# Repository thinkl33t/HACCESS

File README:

Hackspace Access Control/Card Entry Sentry System
=================================================

Access Control nodes for the hackspace

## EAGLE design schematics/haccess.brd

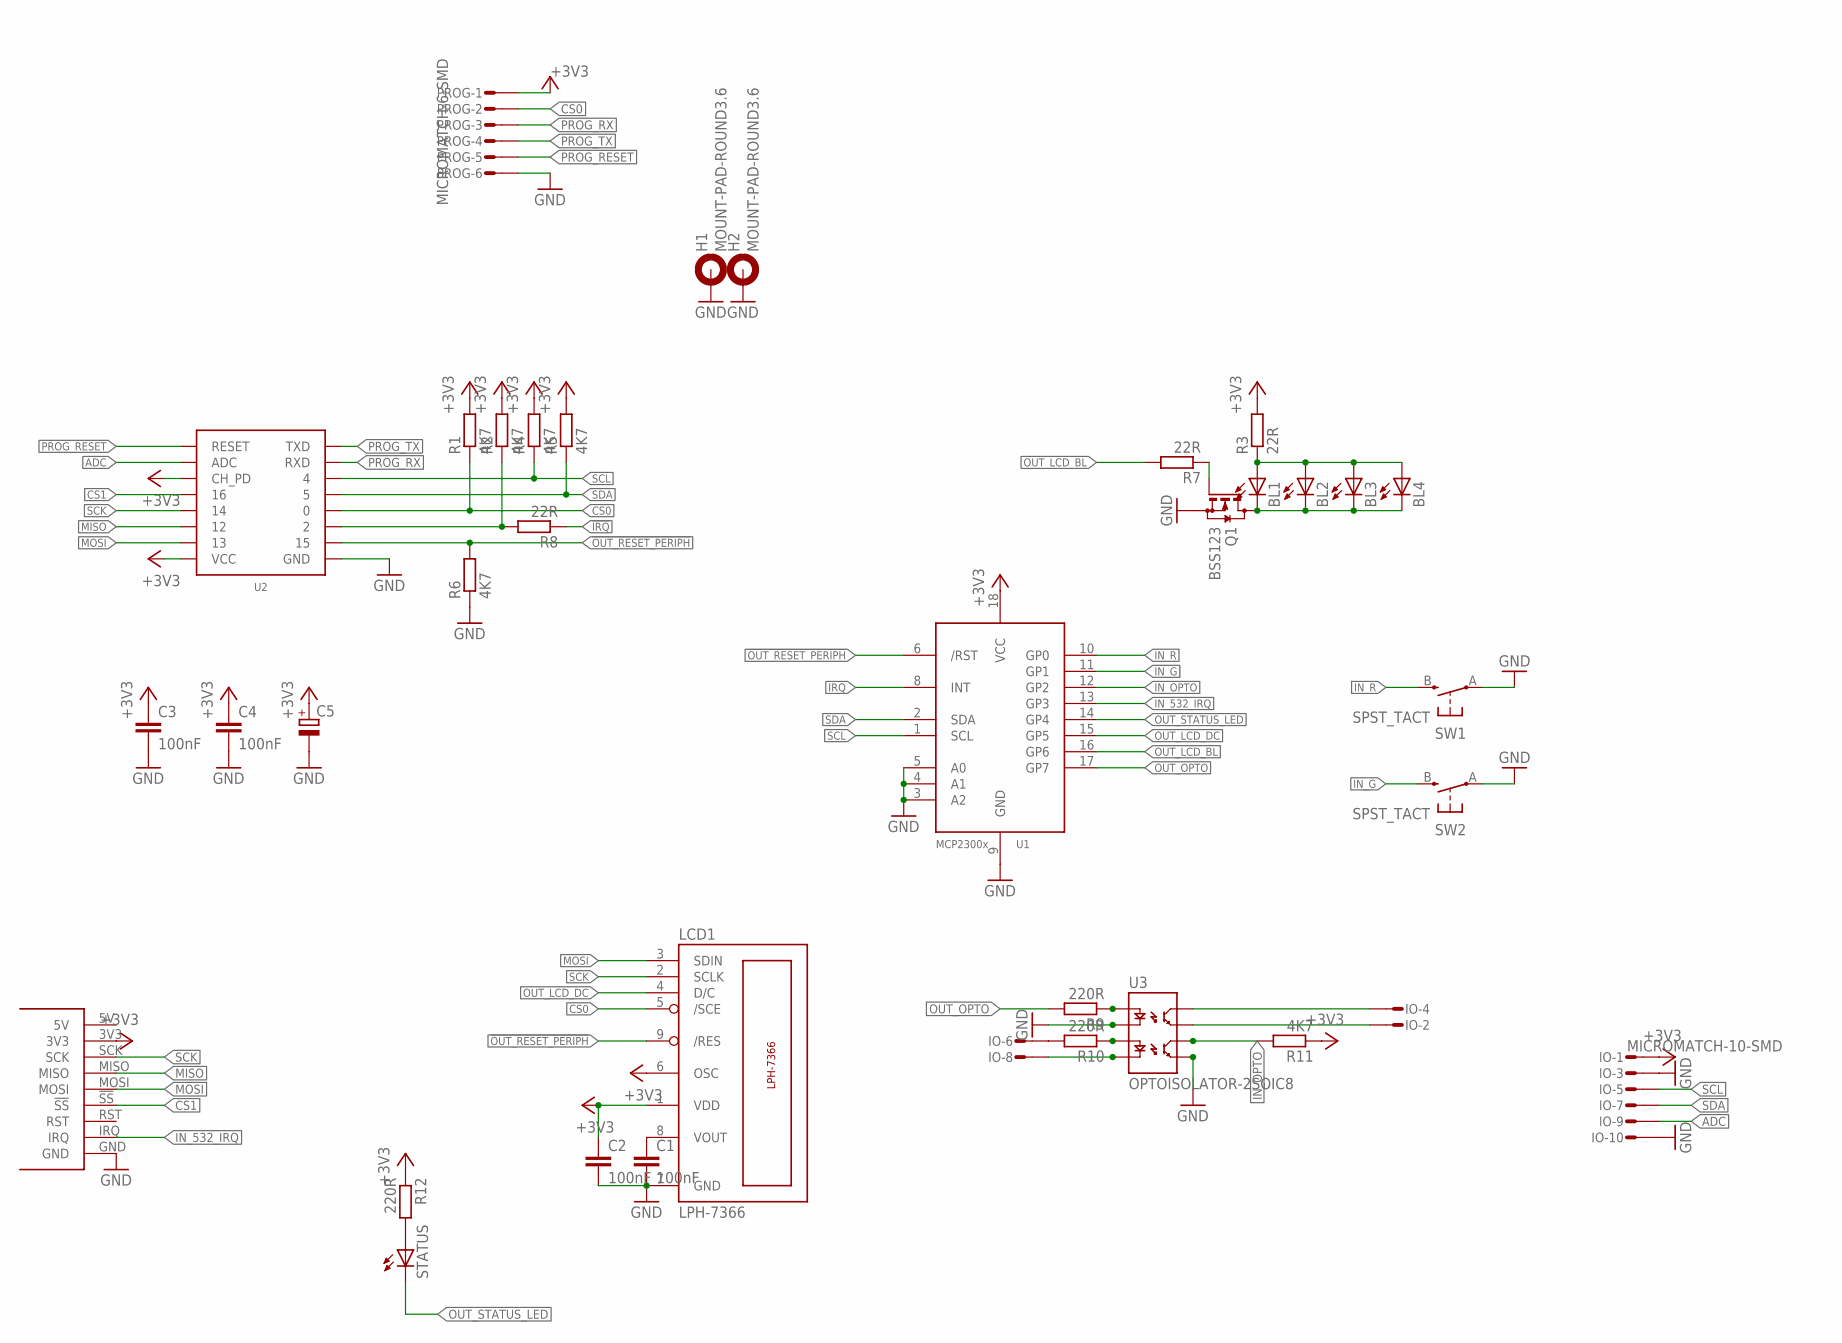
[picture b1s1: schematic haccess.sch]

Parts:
BL1, BL2, BL3, BL4: LEDCHIPLED_0805; CHIPLED_0805
C1, C2, C3, C4: 100nF; C0805K
C5: CPOL-EUSMCB; SMC_B
H1, H2: MOUNT-PAD-ROUND3.6; 3,6-PAD
IO: MICROMATCH-10-SMD
LCD1: LPH-7366
PROG: MICROMATCH-6-SMD
Q1: BSS123; SOT23
R1, R2, R4, R5, R6, R11: 4K7; R0603
R3, R7, R8: 22R; R0603
R9, R10, R12: 220R; R0603
STATUS: LEDCHIP-LED0805; CHIP-LED0805
SW1, SW2: SPST_TACT; SKPMAPE010
U1: MCP2300X/SO; SO18W
U2: ESP826607B; ESP-07B
U3: OPTOISOLATOR-2SOIC8; SO08-2
U$1: PN532SMALLMODULE; SMALL-MODULE

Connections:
!IRQ: R8.1, U1.8 (INT)
!IRQ_1: R2.1, R8.2, U2.GPIO2 (2)
!OUT_RESET_PERIPH: LCD1.9 (/RES), R6.2, U1.6 (/RST), U2.GPIO15 (15)
+3V3: C2.1, C3.1, C4.1, C5.+, IO.1, LCD1.1 (VDD), LCD1.6 (OSC), PROG.1, R1.2, R2.2, R3.2, R4.2, R5.2, R11.1, R12.1, U1.18 (VCC), U2.CH_PD, U2.VCC, U$1.3V3
ADC: IO.9, U2.ADC
CS0: LCD1.5 (/SCE), PROG.2, R1.1, U2.GPIO0 (0)
CS1: U2.GPIO16 (16), U$1.!SS
GND: C1.2, C2.2, C3.2, C4.2, C5.-, H1.B3,6, H2.B3,6, IO.3, IO.10, LCD1.7 (GND), PROG.6, Q1.2 (S), R6.1, SW1.A, SW2.A, U1.3 (A2), U1.4 (A1), U1.5 (A0), U1.9 (GND), U2.GND, U3.2 (C1), U3.5 (EM2), U$1.GND
IN_532_IRQ: U1.13 (GP3), U$1.IRQ
IN_G: SW2.B (S), U1.11 (GP1)
IN_OPTO: R11.2, U1.12 (GP2), U3.6 (CL2)
IN_OPTO_A: IO.6, R10.2
IN_OPTO_C: IO.8, U3.4 (C2)
IN_R: SW1.B (S), U1.10 (GP0)
MISO: U2.GPIO12 (12), U$1.MISO
MOSI: LCD1.3 (SDIN), U2.GPIO13 (13), U$1.MOSI
unnamed: C1.1, LCD1.8 (VOUT)
unnamed: R12.2, STATUS.A
unnamed: R9.1, U3.1 (A1)
unnamed: R10.1, U3.3 (A2)
unnamed: IO.4, U3.8 (CL1)
unnamed: IO.2, U3.7 (EM1)
unnamed: BL1.C, BL2.C, BL3.C, BL4.C, Q1.3 (D)
unnamed: BL1.A, BL2.A, BL3.A, BL4.A, R3.1
unnamed: Q1.1 (G), R7.1
OUT_LCD_BL: R7.2, U1.16 (GP6)
OUT_LCD_DC: LCD1.4 (D/C), U1.15 (GP5)
OUT_OPTO: R9.2, U1.17 (GP7)
OUT_STATUS_LED: STATUS.C, U1.14 (GP4)
PROG_RESET: PROG.5, U2.RESET
PROG_RX: PROG.3, U2.RXD
PROG_TX: PROG.4, U2.TXD
SCK: LCD1.2 (SCLK), U2.GPIO14 (14), U$1.SCK
SCL: IO.5, R4.1, U1.1 (SCL), U2.GPIO4 (4)
SDA: IO.7, R5.1, U1.2 (SDA), U2.GPIO5 (5)

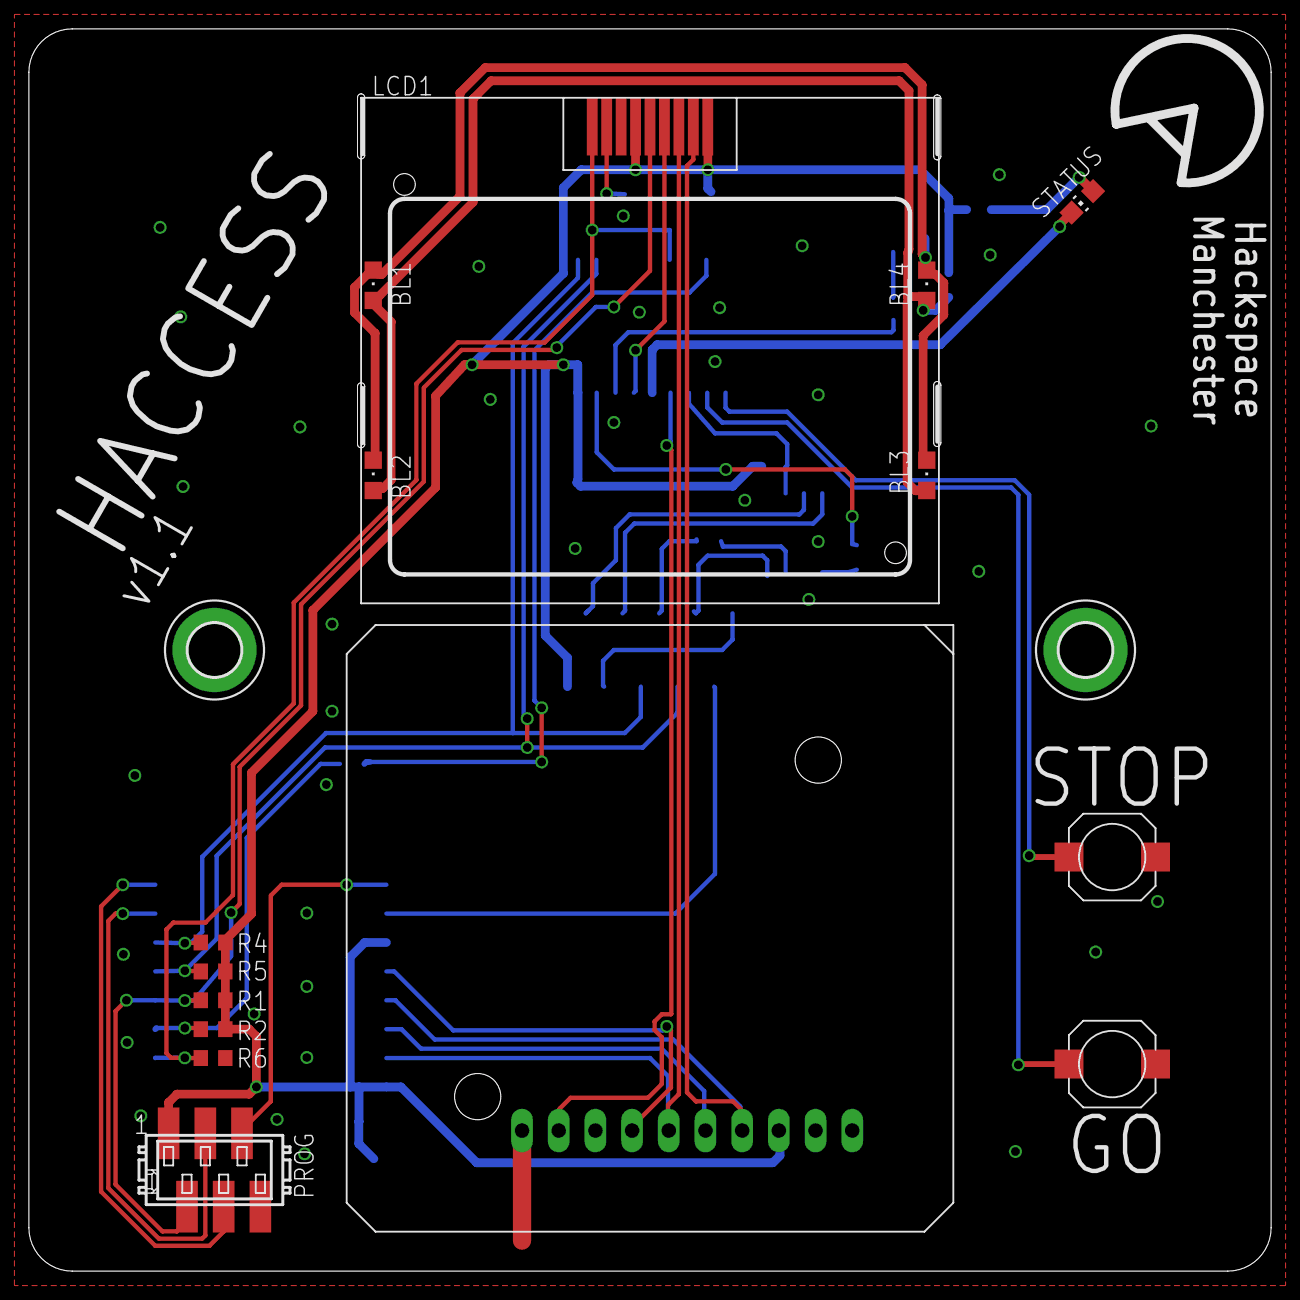
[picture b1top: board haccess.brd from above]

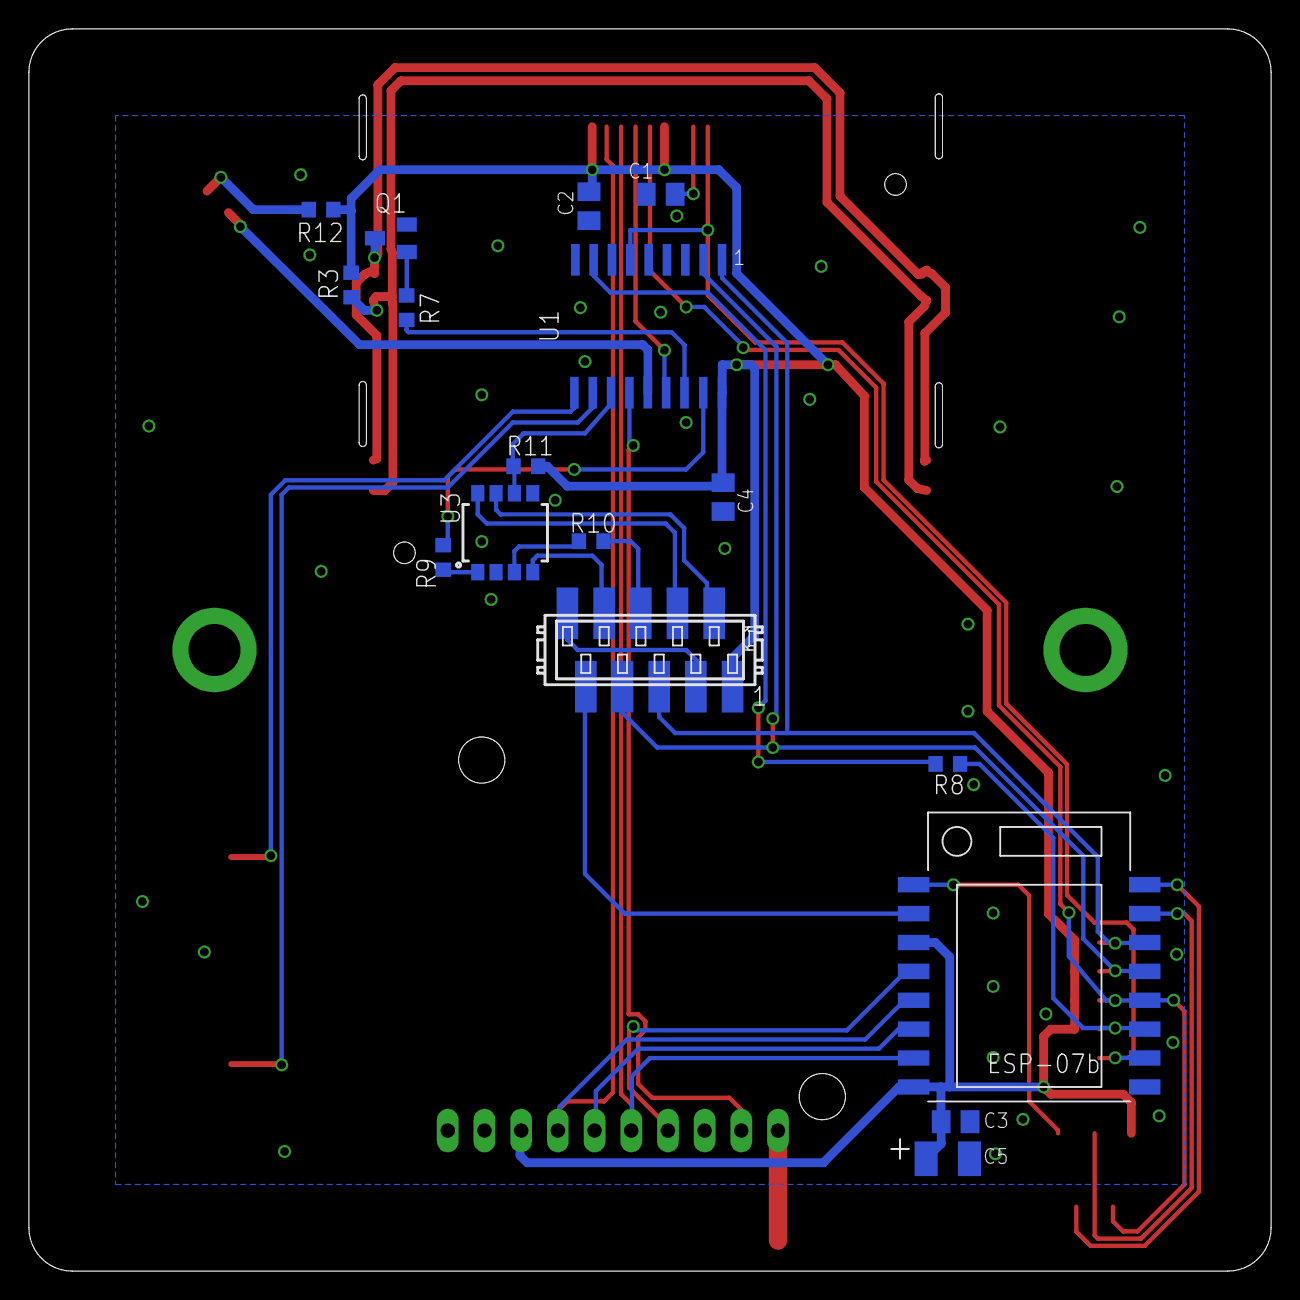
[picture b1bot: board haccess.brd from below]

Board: 2 copper layers, 86.0 x 86.0 mm, 34 parts (17 on the bottom side), 35 nets.

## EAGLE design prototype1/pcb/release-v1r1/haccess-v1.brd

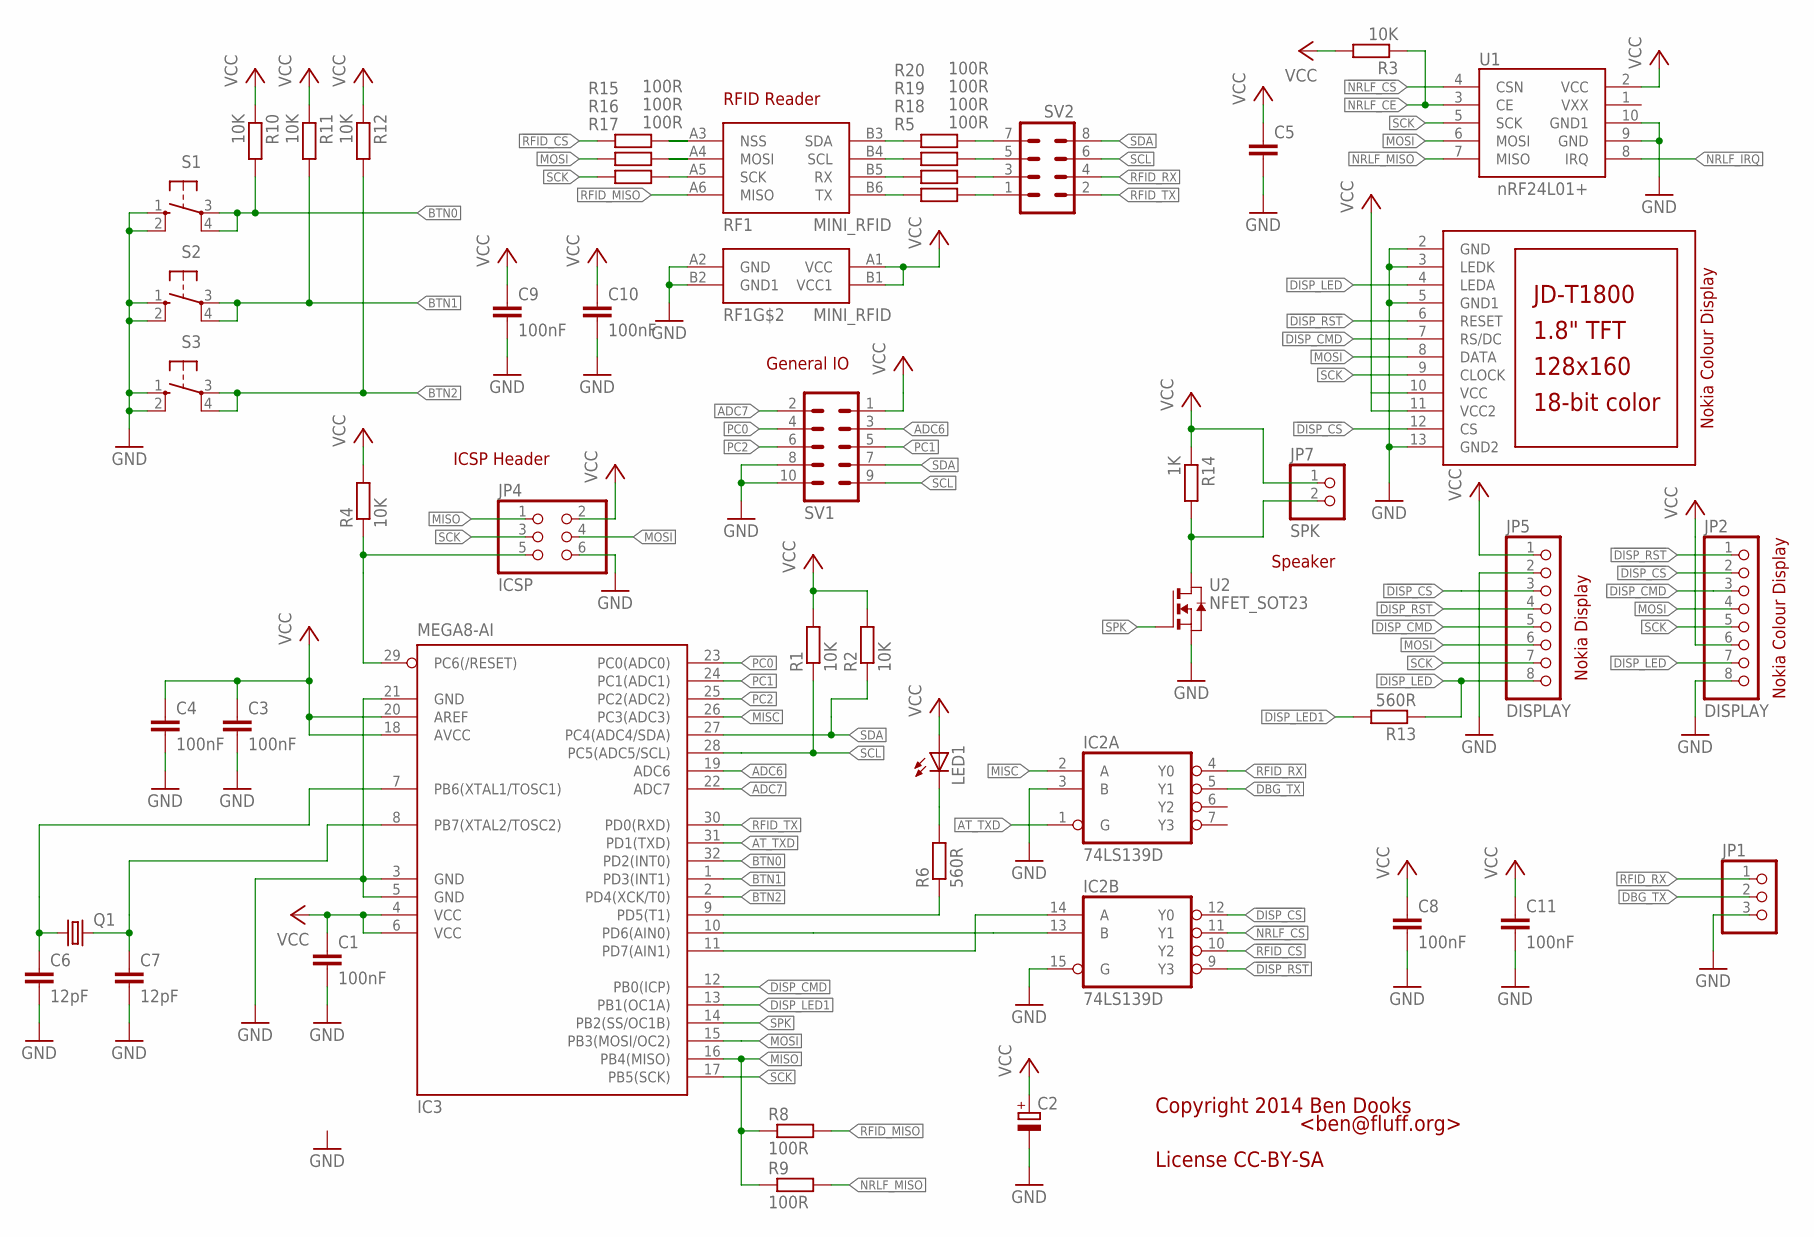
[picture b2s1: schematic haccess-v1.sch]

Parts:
C1, C9, C10: 100nF; C025-030X050
C2: CPOL-EUE2.5-6; E2,5-6
C3, C4, C8, C11: 100nF; C0603K
C5: C-EU025-030X050; C025-030X050
C6, C7: 12pF; C0603K
IC2: 74LS139D; SO16
IC3: MEGA8-AI; TQFP32-08
JP1: PINHD-1X3; 1X03
JP2, JP5: DISPLAY; 1X08
JP4: ICSP; 2X03
JP7: SPK; 1X02
LCD1: JD-T1800
LED1: LED5MM
Q1: CRYSTALHC49S; HC49/S
R1, R2, R3, R4, R10, R11, R12: 10K; R0603
R5, R18, R19, R20: 100R; R0603
R6: 560R; R0603
R8, R9: 100R; 0204/7
R13: 560R; 0204/7
R14: 1K; R0603
R15, R16: 100R; 0207/10
R17: 100R; 0207/7
RF1: MINI_RFID
S1, S2, S3: 10-XX; B3F-10XX
SV1: MA05-2
SV2: MA04-2
U1: NRF24L01+CHINESE-10PIN; CHINESE-10PIN
U2: NFET_SOT23; SOT23

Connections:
!DISP_CS: IC2.12 (Y0), JP2.2, JP5.3, LCD1.12 (CS)
!DISP_RST: IC2.9 (Y3), JP2.1, JP5.4, LCD1.6 (RESET)
!NRLF_CS: IC2.11 (Y1), U1.4 (CSN)
!RESET: IC3.29 (PC6(/RESET)), JP4.5, R4.1
!RFID_CS: IC2.10 (Y2), R15.1
ADC6: IC3.19 (ADC6), SV1.3
ADC7: IC3.22 (ADC7), SV1.2
AT_TXD: IC2.1 (G), IC3.31 (PD1(TXD))
BTN0: IC3.32 (PD2(INT0)), R10.2, S1.3, S1.4 (P1)
BTN1: IC3.1 (PD3(INT1)), R11.2, S2.3, S2.4 (P1)
BTN2: IC3.2 (PD4(XCK/T0)), R12.2, S3.3, S3.4 (P1)
DBG_TX: IC2.5 (Y1), JP1.2
DISP_CMD: IC3.12 (PB0(ICP)), JP2.3, JP5.5, LCD1.7 (RS/DC)
DISP_LED: JP2.7, JP5.8, LCD1.4 (LEDA), R13.1
DISP_LED1: IC3.13 (PB1(OC1A)), R13.2
GND: C1.2, C2.-, C3.2, C4.2, C5.2, C6.2, C7.2, C8.2, C9.2, C10.2, C11.2, IC2.3 (B), IC2.8 (GND), IC2.15 (G), IC3.3 (GND), IC3.5 (GND), IC3.21 (GND), JP1.3, JP2.8, JP4.6, JP5.2, LCD1.2 (GND), LCD1.3 (LEDK), LCD1.5 (GND1), LCD1.13 (GND2), RF1.A2 (GND), RF1.B2 (GND1), S1.1 (S), S1.2 (S1), S2.1 (S), S2.2 (S1), S3.1 (S), S3.2 (S1), SV1.8, SV1.10, U1.9 (GND), U1.10 (GND1), U2.2 (S)
LED: IC3.9 (PD5(T1)), R6.1
LED1: LED1.K (C), R6.2
MISC: IC2.2 (A), IC3.26 (PC3(ADC3))
MISO: IC3.16 (PB4(MISO)), JP4.1, R8.1, R9.1
MOSI: IC3.15 (PB3(MOSI/OC2)), JP2.4, JP4.4, JP5.6, LCD1.8 (DATA), R16.1, U1.6 (MOSI)
unnamed: R17.2, RF1.A5 (SCK)
unnamed: R16.2, RF1.A4 (MOSI)
unnamed: R15.2, RF1.A3 (NSS)
unnamed: R5.1, RF1.B6 (TX)
unnamed: R18.1, RF1.B5 (RX)
unnamed: R19.1, RF1.B4 (SCL)
unnamed: R20.1, RF1.B3 (SDA)
unnamed: R20.2, SV2.7
unnamed: IC2.13 (B), IC3.10 (PD6(AIN0))
unnamed: R19.2, SV2.5
unnamed: IC2.14 (A), IC3.11 (PD7(AIN1))
unnamed: R18.2, SV2.3
unnamed: R5.2, SV2.1
NRLF_CE: R3.1, U1.3 (CE)
NRLF_IRQ: U1.8 (IRQ)
NRLF_MISO: R9.2, U1.7 (MISO)
PC0: IC3.23 (PC0(ADC0)), SV1.4
PC1: IC3.24 (PC1(ADC1)), SV1.5
PC2: IC3.25 (PC2(ADC2)), SV1.6
RFID_MISO: R8.2, RF1.A6 (MISO)
RFID_RX: IC2.4 (Y0), JP1.1, SV2.4
RFID_TX: IC3.30 (PD0(RXD)), SV2.2
SCK: IC3.17 (PB5(SCK)), JP2.5, JP4.3, JP5.7, LCD1.9 (CLOCK), R17.1, U1.5 (SCK)
SCL: IC3.28 (PC5(ADC5/SCL)), R1.1, SV1.9, SV2.6
SDA: IC3.27 (PC4(ADC4/SDA)), R2.1, SV1.7, SV2.8
SPK: IC3.14 (PB2(SS/OC1B)), U2.1 (G)
SPK1: JP7.2, R14.2, U2.3 (D)
VCC: C1.1, C2.+, C3.1, C4.1, C5.1, C8.1, C9.1, C10.1, C11.1, IC2.16 (VCC), IC3.4 (VCC), IC3.6 (VCC), IC3.18 (AVCC), IC3.20 (AREF), JP2.6, JP4.2, JP5.1, JP7.1, LCD1.10 (VCC), LCD1.11 (VCC2), LED1.A, R1.2, R2.2, R3.2, R4.2, R10.1, R11.1, R12.1, R14.1, RF1.A1 (VCC), RF1.B1 (VCC1), SV1.1, U1.2 (VCC)
XT1: C6.1, IC3.7 (PB6(XTAL1/TOSC1)), Q1.1
XT2: C7.1, IC3.8 (PB7(XTAL2/TOSC2)), Q1.2

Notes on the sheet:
RFID Reader
General IO
Nokia Display
ICSP Header
Speaker
Copyright 2014 Ben Dooks
<ben@fluff.org>
License CC-BY-SA
Nokia Colour Display

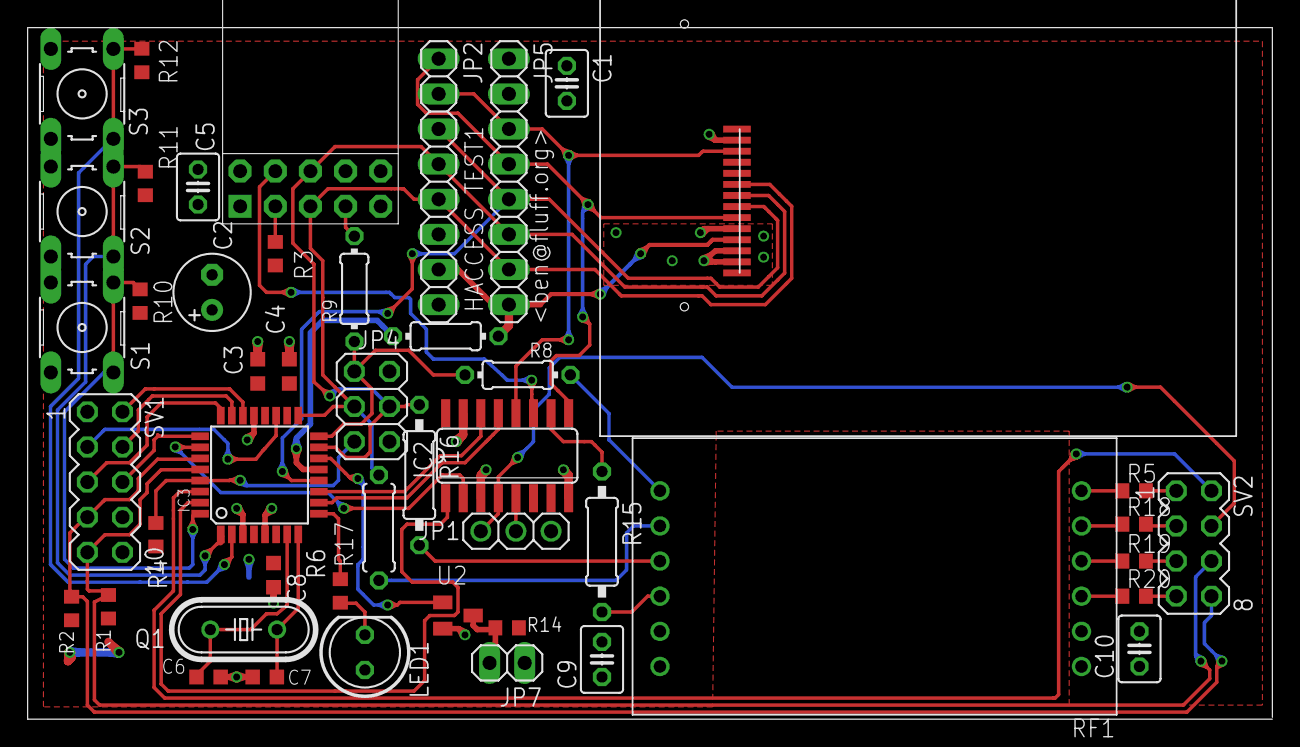
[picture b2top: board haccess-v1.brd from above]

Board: 2 copper layers, 90.0 x 50.0 mm, 48 parts (1 on the bottom side), 50 nets.

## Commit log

2013-10-22 Initial Commit - Pattress plate v0.01
2013-10-22 Added pattress box, split off rounded rect etc into its own library. Created LCD and RFID models.
2013-10-23 Rounded off corners, fixed rfid hole diameter
2014-05-21 Updated 3d model to new parts. Added Buttons
2014-05-21 added screw to haccess
2014-05-21 Added blue button for training
2014-10-31 prototype pcb1
2015-05-26 HACCESS Schematic
    v1 of HACCESS board design. needs USB protection adding, along
    with possibly FM1701 chip & componants directly on the PCB.
2015-05-26 Merged master
2015-05-28 First version of haccess PCB
    Has components in correct places, some minimal routing.
    Modified pattress plate to add correclty spaced holes for bolting haccess to plate.
2015-09-10 Imported DXF of outline, got all important tuff into place, began routing
2015-09-10 Modified pattress plate layout to add pcb size etc, exported PCB
2015-12-09 Routed board
2015-12-09 Ran DRC, added holes for mounting LCD
2015-12-10 Added extra decoupling caps to ESP and MCP, added resistor to IRQ line, increased size of +3V3 lines, improved routing, fixed ground plane under ESP, changed switches to SKPMAPE010
2015-12-10 Added gerber files for production
2015-12-11 Added tant cap, increased size of 3V lines, improved documentation silks
2015-12-21 Board as purchased
2015-12-22 Changed backlight to use 0805 pads - still usable with 0603 parts, but easier to solder
2015-12-22 Moved Status LED onto pin expander, i2c and LCD reset pins onto pin 15
2015-12-23 Increased status LED track sizes, changed 0805 leds to consistent package
2015-12-23 Increased aerial keepout, routing tweaks

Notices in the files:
parts and their libraries:
SparkFun-DiscreteSemi: Licensing: Creative Commons ShareAlike 4.0 International - https://creativecommons.org/licenses/by-sa/4.0
